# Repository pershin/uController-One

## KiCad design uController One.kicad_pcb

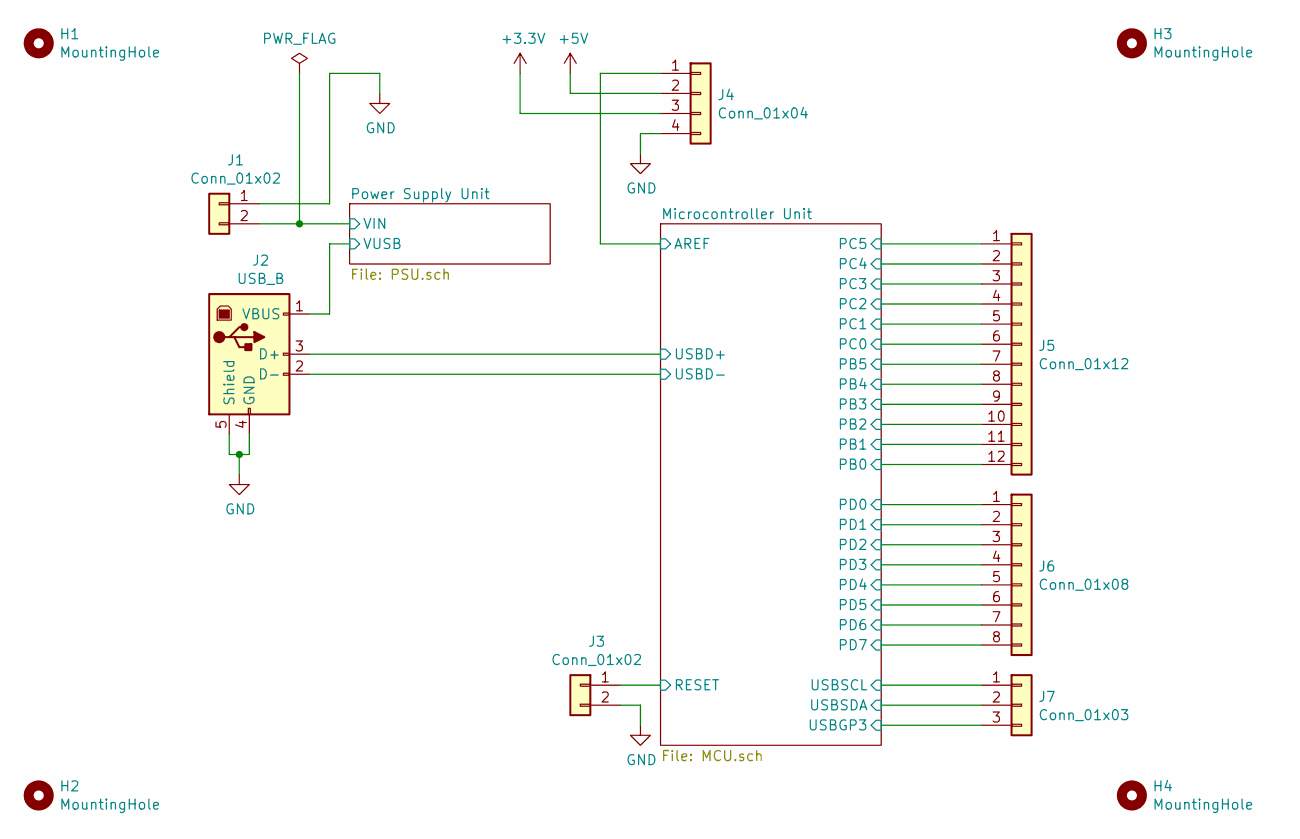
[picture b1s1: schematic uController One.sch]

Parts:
H1, H2, H3, H4: MountingHole; MountingHole_3.2mm_M3_Pad_Via
J1: Conn_01x02; JST_VH_B2P-VH_1x02_P3.96mm_Vertical
J2: USB_B; USB_B_OST_USB-B1HSxx_Horizontal
J3: Conn_01x02; PinHeader_1x02_P2.54mm_Vertical
J4: Conn_01x04; PinSocket_1x04_P2.54mm_Vertical
J5: Conn_01x12; PinSocket_1x12_P2.54mm_Vertical
J6: Conn_01x08; PinSocket_1x08_P2.54mm_Vertical
J7: Conn_01x03; PinSocket_1x03_P2.54mm_Vertical

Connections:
+3V3: J4.3; also elsewhere on the board
+5V: J4.2; also elsewhere on the board
/Microcontroller Unit/AREF: J4.1; also elsewhere on the board
/Microcontroller Unit/PB0: J5.12; also elsewhere on the board
/Microcontroller Unit/PB1: J5.11; also elsewhere on the board
/Microcontroller Unit/PB2: J5.10; also elsewhere on the board
/Microcontroller Unit/PB3: J5.9; also elsewhere on the board
/Microcontroller Unit/PB4: J5.8; also elsewhere on the board
/Microcontroller Unit/PB5: J5.7; also elsewhere on the board
/Microcontroller Unit/PC0: J5.6; also elsewhere on the board
/Microcontroller Unit/PC1: J5.5; also elsewhere on the board
/Microcontroller Unit/PC2: J5.4; also elsewhere on the board
/Microcontroller Unit/PC3: J5.3; also elsewhere on the board
/Microcontroller Unit/PC4: J5.2; also elsewhere on the board
/Microcontroller Unit/PC5: J5.1; also elsewhere on the board
/Microcontroller Unit/PD2: J6.3; also elsewhere on the board
/Microcontroller Unit/PD3: J6.4; also elsewhere on the board
/Microcontroller Unit/PD4: J6.5; also elsewhere on the board
/Microcontroller Unit/PD5: J6.6; also elsewhere on the board
/Microcontroller Unit/PD6: J6.7; also elsewhere on the board
/Microcontroller Unit/PD7: J6.8; also elsewhere on the board
/Microcontroller Unit/USBD+: J2.3 (D+); also elsewhere on the board
/Microcontroller Unit/USBD-: J2.2 (D-); also elsewhere on the board
/Microcontroller Unit/USBGP3: J7.3; also elsewhere on the board
/Microcontroller Unit/USBSCL: J7.1; also elsewhere on the board
/Microcontroller Unit/USBSDA: J7.2; also elsewhere on the board
/Power Supply Unit/VIN: J1.2; also elsewhere on the board
/Power Supply Unit/VUSB: J2.1 (VBUS); also elsewhere on the board
GND: J1.1, J2.4 (GND), J2.5 (Shield), J3.2, J4.4; also elsewhere on the board
PD0: J6.1; also elsewhere on the board
PD1: J6.2; also elsewhere on the board
RESET: J3.1; also elsewhere on the board

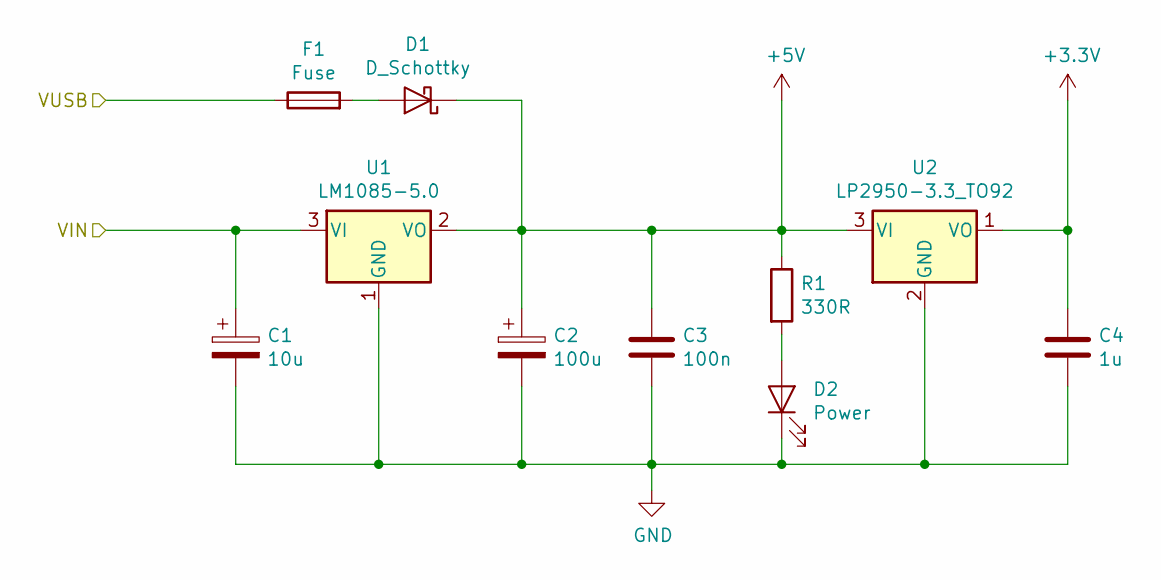
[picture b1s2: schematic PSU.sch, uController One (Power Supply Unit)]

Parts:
C1: 10u; CP_Radial_D8.0mm_P3.50mm
C2: 100u; CP_Radial_D8.0mm_P3.50mm
C3: 100n; C_Disc_D5.0mm_W2.5mm_P2.50mm
C4: 1u; C_Disc_D6.0mm_W4.4mm_P5.00mm
D1: D_Schottky; D_DO-41_SOD81_P10.16mm_Horizontal
D2: Power; LED_D5.0mm
F1: Fuse; Fuse_Bourns_MF-RHT050
R1: 330R; R_Axial_DIN0207_L6.3mm_D2.5mm_P10.16mm_Horizontal
U1: LM1085-5.0; TO-220-3_Vertical
U2: LP2950-3.3_TO92; TO-92_Inline

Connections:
+3V3: C4.1, U2.1 (VO); also elsewhere on the board
+5V: C2.1, C3.1, D1.1 (K), R1.1, U1.2 (VO), U2.3 (VI); also elsewhere on the board
/Power Supply Unit/VIN: C1.1, U1.3 (VI); also elsewhere on the board
/Power Supply Unit/VUSB: F1.1; also elsewhere on the board
GND: C1.2, C2.2, C3.2, C4.2, D2.1 (K), U1.1 (GND), U2.2 (GND); also elsewhere on the board
unnamed: D1.2 (A), F1.2
unnamed: D2.2 (A), R1.2

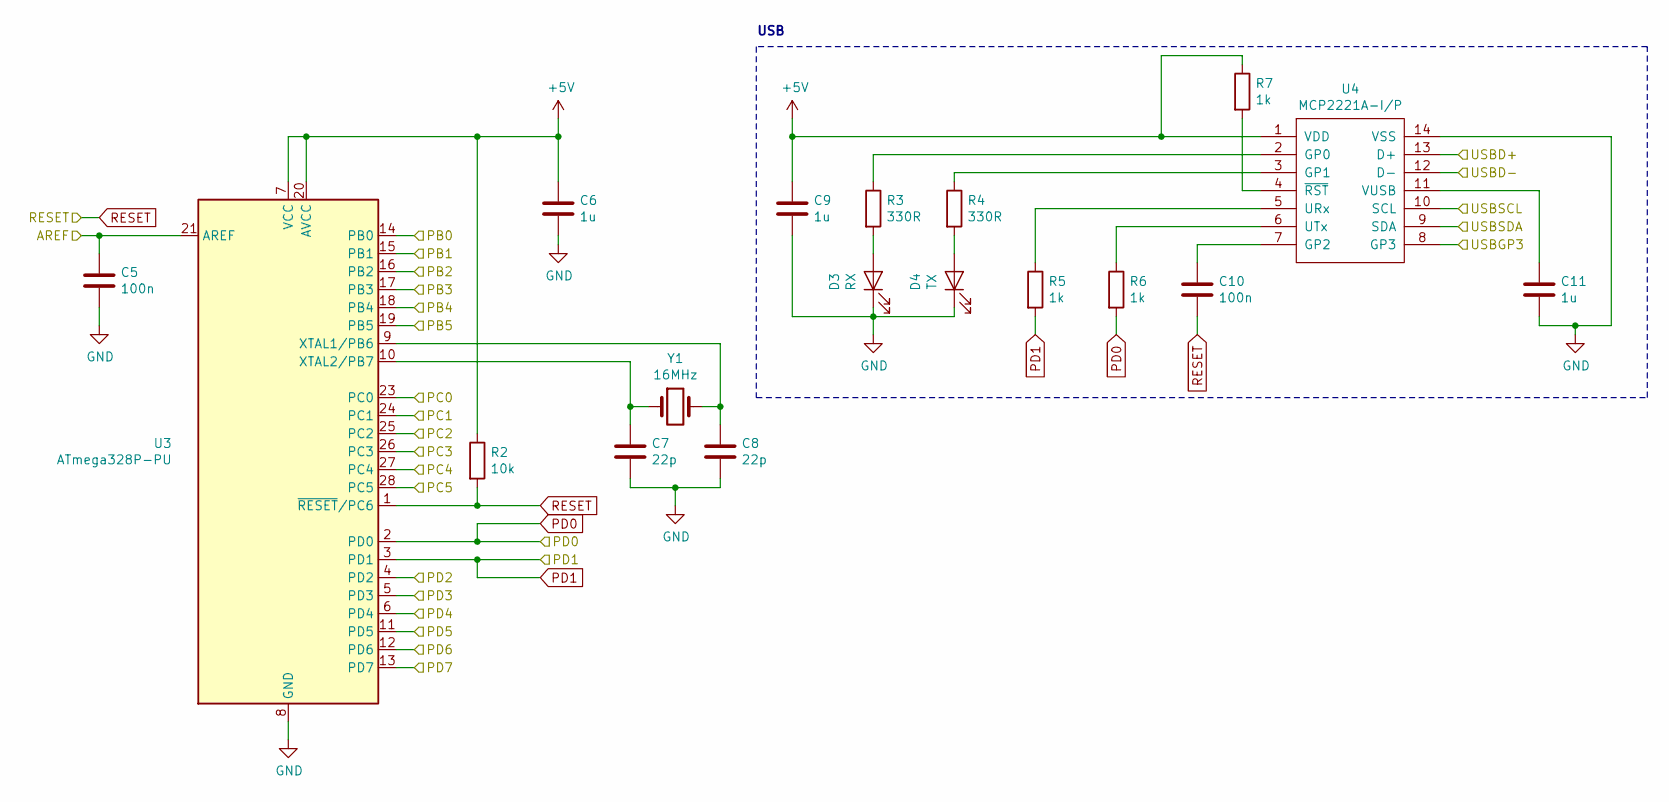
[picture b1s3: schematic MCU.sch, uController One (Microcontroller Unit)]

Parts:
C5, C10: 100n; C_Disc_D5.0mm_W2.5mm_P2.50mm
C6, C9, C11: 1u; C_Disc_D6.0mm_W4.4mm_P5.00mm
C7, C8: 22p; C_Disc_D4.3mm_W1.9mm_P5.00mm
D3: RX; LED_D5.0mm
D4: TX; LED_D5.0mm
R2: 10k; R_Axial_DIN0207_L6.3mm_D2.5mm_P10.16mm_Horizontal
R3, R4: 330R; R_Axial_DIN0207_L6.3mm_D2.5mm_P10.16mm_Horizontal
R5, R6, R7: 1k; R_Axial_DIN0207_L6.3mm_D2.5mm_P10.16mm_Horizontal
U3: ATmega328P-PU; DIP-28_W7.62mm_Socket
U4: MCP2221A-I/P; DIP-14_W7.62mm_Socket
Y1: 16MHz; Crystal_HC49-U_Vertical

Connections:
+5V: C6.1, C9.1, R2.1, R7.1, U3.7 (VCC), U3.20 (AVCC), U4.1 (VDD); also elsewhere on the board
/Microcontroller Unit/AREF: C5.1, U3.21 (AREF); also elsewhere on the board
/Microcontroller Unit/PB0: U3.14 (PB0); also elsewhere on the board
/Microcontroller Unit/PB1: U3.15 (PB1); also elsewhere on the board
/Microcontroller Unit/PB2: U3.16 (PB2); also elsewhere on the board
/Microcontroller Unit/PB3: U3.17 (PB3); also elsewhere on the board
/Microcontroller Unit/PB4: U3.18 (PB4); also elsewhere on the board
/Microcontroller Unit/PB5: U3.19 (PB5); also elsewhere on the board
/Microcontroller Unit/PC0: U3.23 (PC0); also elsewhere on the board
/Microcontroller Unit/PC1: U3.24 (PC1); also elsewhere on the board
/Microcontroller Unit/PC2: U3.25 (PC2); also elsewhere on the board
/Microcontroller Unit/PC3: U3.26 (PC3); also elsewhere on the board
/Microcontroller Unit/PC4: U3.27 (PC4); also elsewhere on the board
/Microcontroller Unit/PC5: U3.28 (PC5); also elsewhere on the board
/Microcontroller Unit/PD2: U3.4 (PD2); also elsewhere on the board
/Microcontroller Unit/PD3: U3.5 (PD3); also elsewhere on the board
/Microcontroller Unit/PD4: U3.6 (PD4); also elsewhere on the board
/Microcontroller Unit/PD5: U3.11 (PD5); also elsewhere on the board
/Microcontroller Unit/PD6: U3.12 (PD6); also elsewhere on the board
/Microcontroller Unit/PD7: U3.13 (PD7); also elsewhere on the board
/Microcontroller Unit/USBD+: U4.13 (D+); also elsewhere on the board
/Microcontroller Unit/USBD-: U4.12 (D-); also elsewhere on the board
/Microcontroller Unit/USBGP3: U4.8 (GP3); also elsewhere on the board
/Microcontroller Unit/USBSCL: U4.10 (SCL); also elsewhere on the board
/Microcontroller Unit/USBSDA: U4.9 (SDA); also elsewhere on the board
GND: C5.2, C6.2, C7.2, C8.2, C9.2, C11.2, D3.1 (K), D4.1 (K), U3.8 (GND), U3.22 (GND), U4.14 (VSS); also elsewhere on the board
unnamed: C7.1, U3.10 (XTAL2/PB7), Y1.1
unnamed: C8.1, U3.9 (XTAL1/PB6), Y1.2
unnamed: C10.1, U4.7 (GP2)
unnamed: C11.1, U4.11 (VUSB)
unnamed: D3.2 (A), R3.2
unnamed: D4.2 (A), R4.2
unnamed: R3.1, U4.2 (GP0)
unnamed: R4.1, U4.3 (GP1)
unnamed: R5.1, U4.5 (URx)
unnamed: R6.1, U4.6 (UTx)
unnamed: R7.2, U4.4 (~RST)
PD0: R6.2, U3.2 (PD0); also elsewhere on the board
PD1: R5.2, U3.3 (PD1); also elsewhere on the board
RESET: C10.2, R2.2, U3.1 (~RESET~/PC6); also elsewhere on the board

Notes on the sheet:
USB

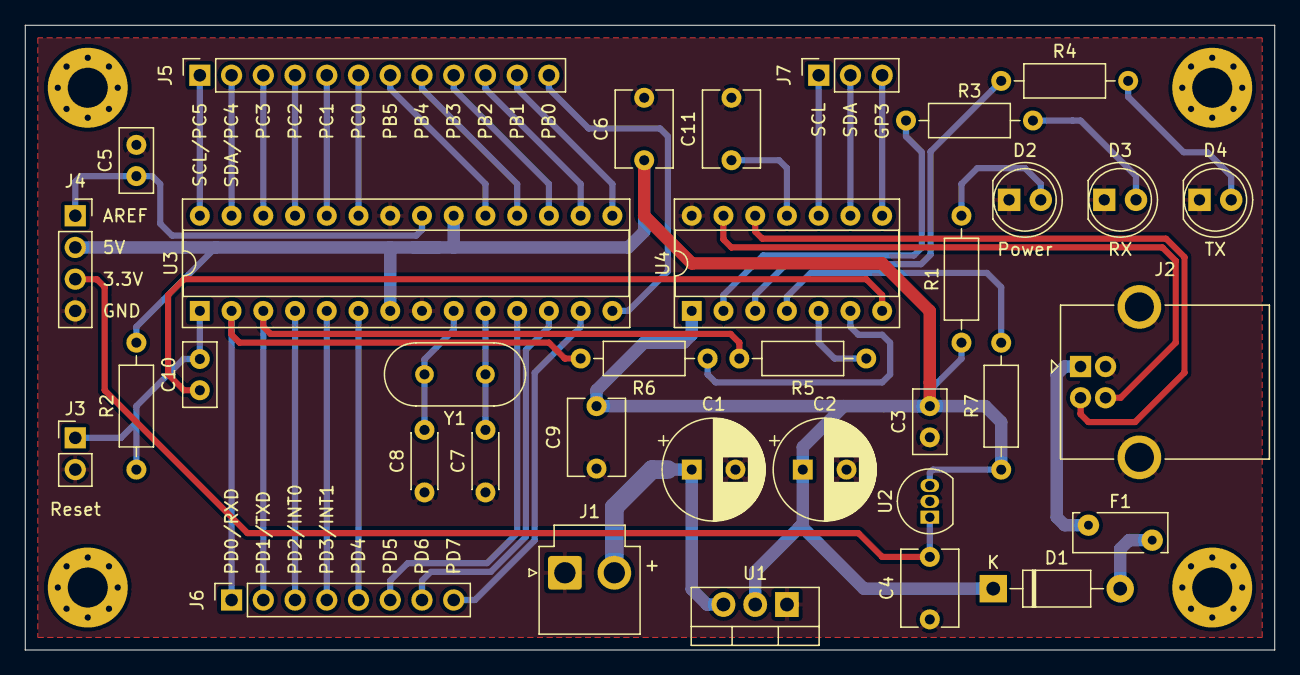
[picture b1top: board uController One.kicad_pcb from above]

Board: 2 copper layers, 100.0 x 50.0 mm, 39 parts (0 on the bottom side), 45 nets.

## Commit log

2019-12-11 Added Gerber and drl files.
2019-12-24 Added photos.
